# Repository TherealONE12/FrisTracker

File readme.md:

# FrisTracker

A GPS tracking device embedded in an Frisbee disc to capture real-time movement data during games.

## What it does

FrisTracker records GPS coordinates during a frisbee game and wirelessly transmits them to a laptop in real-time. The data can show throwing patterns, strategies, and field coverage throughout a match.

## Why it exists

At my Youth club, we are obsesssed with Ultimate Frisbee. However, as we have lost last years anual Cup to another youth club, we were all devestad. So, I Build FrisTracker! It can help us to Analyze our Training games, and spot weaknesses in our Defense (Or more importantly, weaknesses in our Enemys defenses wich we can then exploit to get an very fair advantage)

Also, tracking a flying disc at 60 mph is just fun.

## Hardware

The tracker fits inside a Frisbee disc and includes:
- **ESP32-PICO-V3-02** microcontroller for GPS processing and wireless transmission
- **NEO-6M GPS module** with external antenna for position tracking
- **NRF24L01+PA+LNA** 2.4GHz radio module for real-time data transmission

A separate receiver module plugs into your laptop and captures the incoming GPS data.

The PCB design files are in `hardware/kicad/`. Gerber files for manufacturing are in `hardware/gerbers/fristracker-gerbers.zip`.

## Bill of Materials

| Part | Purpose | Qty | Unit Price | Total | Vendor |
|------|---------|-----|------------|-------|--------|
| [ESP32-PICO-V3-02](https://de.aliexpress.com/item/1005011934924363.html) | Microcontroller (comes as 2-pack) | 1 | $15.11 | $15.11 | AliExpress |
| [CH340E](https://de.aliexpress.com/item/1005012848940494.html) | USB-to-serial converter | 2 | $6.18 | $12.36 | AliExpress |
| [TLV75733PDRV](https://www.ti.com/product/TLV757P) | 3.3V voltage regulator | 2 | $0.44 | $0.88 | Texas Instruments |
| [NRF24L01+PA+LNA](https://de.aliexpress.com/item/1005008770982853.html) | 2.4GHz wireless transceiver | 2 | $3.84 | $7.68 | AliExpress |
| [NEO-6M GPS](https://de.aliexpress.com/item/1005013019346751.html) | GPS module | 1 | $3.42 | $3.42 | AliExpress |
| [Coin cell holder](https://www.sparkfun.com/coin-cell-battery-holder-12mm-smd.html) | Battery holder for GPS backup | 1 | $0.80 | $0.80 | SparkFun |
| [SMA edge connector](https://www.digikey.com/en/products/detail/rf-solutions/CON-SMA-EDGE-S/5845767) | GPS antenna connector | 1 | $2.75 | $2.75 | DigiKey |
| [GPS antenna](https://de.aliexpress.com/item/1005008618780803.html) | External GPS antenna | 1 | $3.45 | $3.45 | AliExpress |
| | | | **Subtotal** | **$46.45** | |
| | | | **Tax & shipping** | **$15.00** | |
| | | | **Total** | **$61.45** | |

Tax and shipping May vary at your place! - Not included Bill of PCB Files.

## Firmware

The tracker and receiver each run separate Arduino sketches:
- `firmware/tracker.ino` — runs on the disc, reads GPS and transmits data
- `firmware/receiver.ino` — runs on the laptop side, receives and logs data

## Status

Hardware design is complete. Firmware is functional but basic. Building instructions coming soon.

## Project structure

```
FrisTracker/
├── hardware/
│   ├── gerbers/           # Manufacturing files
│   ├── kicad/            # PCB design files
│   └── BOM_base.csv      # Component list
├── firmware/
│   ├── tracker.ino       # Disc-side firmware
│   └── receiver.ino      # Laptop-side firmware
└── docs/
    └── JOURNAL.md        # Development log
```

## License

Open source hardware project. Built as part of Half Life.

Built by Jakob. With lots of <3 and some Bugs :)

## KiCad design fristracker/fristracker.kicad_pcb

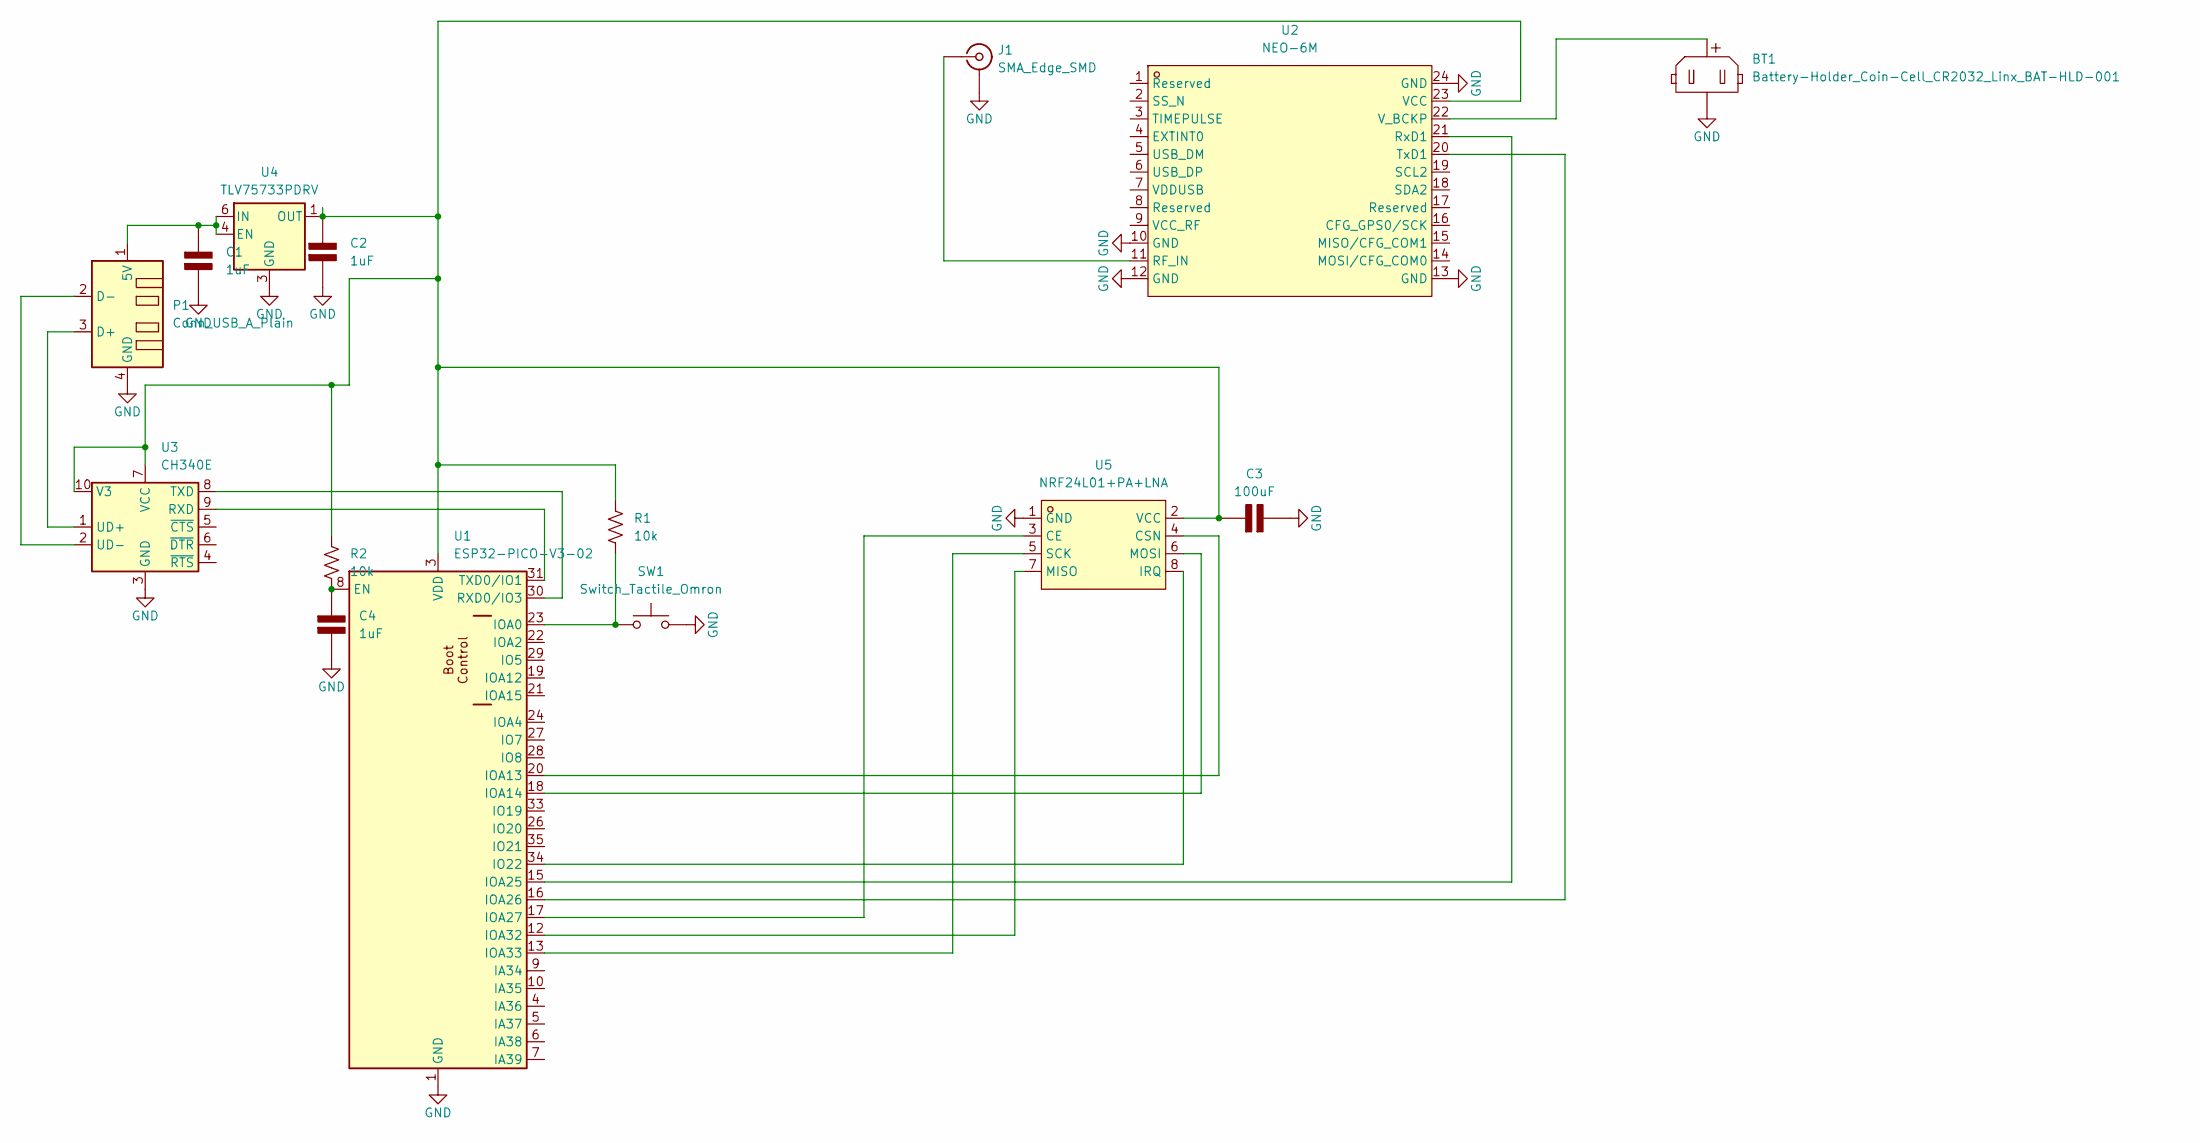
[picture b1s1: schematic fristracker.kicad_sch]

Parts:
BT1: Battery-Holder_Coin-Cell_CR2032_Linx_BAT-HLD-001
C1: 1uF; C_Disc_D5.0mm_W2.5mm_P5.00mm; Rating V
C2, C4: 1uF; C_Disc_D4.3mm_W1.9mm_P5.00mm; Rating V
C3: 100uF; CP_Radial_Tantal_D5.0mm_P5.00mm; Rating V
J1: SMA_Edge_SMD
P1: Conn_USB_A_Plain
R1, R2: 10k; R_0603_1608Metric
SW1: Switch_Tactile_Omron; Button_Omron_B3SN_6.0x6.0mm
U1: ESP32-PICO-V3-02; ESP32-PICO-MINI
U2: NEO-6M; GPSM-SMD_24P-L16.0-W12.2-P1.10; MPN NEO-6M; LCSC Part C2927633
U3: CH340E; MSOP-10_3x3mm_P0.5mm
U4: TLV75733PDRV; WDFN-6_2x2mm
U5: NRF24L01+PA+LNA; COMM-TH_L41.0-W15.5-P2.54_NRF24L01; MPN nRF24L01+PA+LNA; LCSC Part C9900187674

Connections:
GND: BT1.2 (-), C1.2 (-), C2.2 (-), C3.2 (-), C4.2 (-), J1.2 (Ext), P1.4 (GND), SW1.2, U1.1 (GND), U1.2 (GND), U1.11 (GND), U1.14 (GND), U1.36 (GND), U1.37 (GND), U1.38 (GND), U1.39 (GND), U1.40 (GND), U1.41 (GND), U1.42 (GND), U1.43 (GND), U1.44 (GND), U1.45 (GND), U1.46 (GND), U1.47 (GND), U1.48 (GND), U1.49.1 (GND), U1.49.2 (GND), U1.49.3 (GND), U1.49.4 (GND), U1.49.5 (GND), U1.49.6 (GND), U1.49.7 (GND), U1.49.8 (GND), U1.49.9 (GND), U1.50 (GND), U1.51 (GND), U1.52 (GND), U1.53 (GND), U2.10 (GND), U2.12 (GND), U2.13 (GND), U2.24 (GND), U3.3 (GND), U4.3 (GND), U4.7 (GND), U5.1 (GND)
unnamed: BT1.1 (+), U2.22 (V_BCKP)
unnamed: C1.1 (+), P1.1 (5V), U4.4 (EN), U4.6 (IN)
unnamed: C2.1 (+), C3.1 (+), R1.1, R2.1, U1.3 (VDD), U2.23 (VCC), U3.7 (VCC), U3.10 (V3), U4.1 (OUT), U5.2 (VCC)
unnamed: C4.1 (+), R2.2, U1.8 (EN)
unnamed: J1.1 (In), U2.11 (RF_IN)
unnamed: P1.3 (D+), U3.1 (UD+)
unnamed: P1.2 (D-), U3.2 (UD-)
unnamed: U1.34 (IO22), U5.8 (IRQ)
unnamed: R1.2, SW1.1, U1.23 (IOA0)
unnamed: U1.20 (IOA13), U5.4 (CSN)
unnamed: U1.18 (IOA14), U5.6 (MOSI)
unnamed: U1.15 (IOA25), U2.21 (RxD1)
unnamed: U1.16 (IOA26), U2.20 (TxD1)
unnamed: U1.17 (IOA27), U5.3 (CE)
unnamed: U1.12 (IOA32), U5.7 (MISO)
unnamed: U1.13 (IOA33), U5.5 (SCK)
unnamed: U1.30 (RXD0/IO3), U3.8 (TXD)
unnamed: U1.31 (TXD0/IO1), U3.9 (RXD)

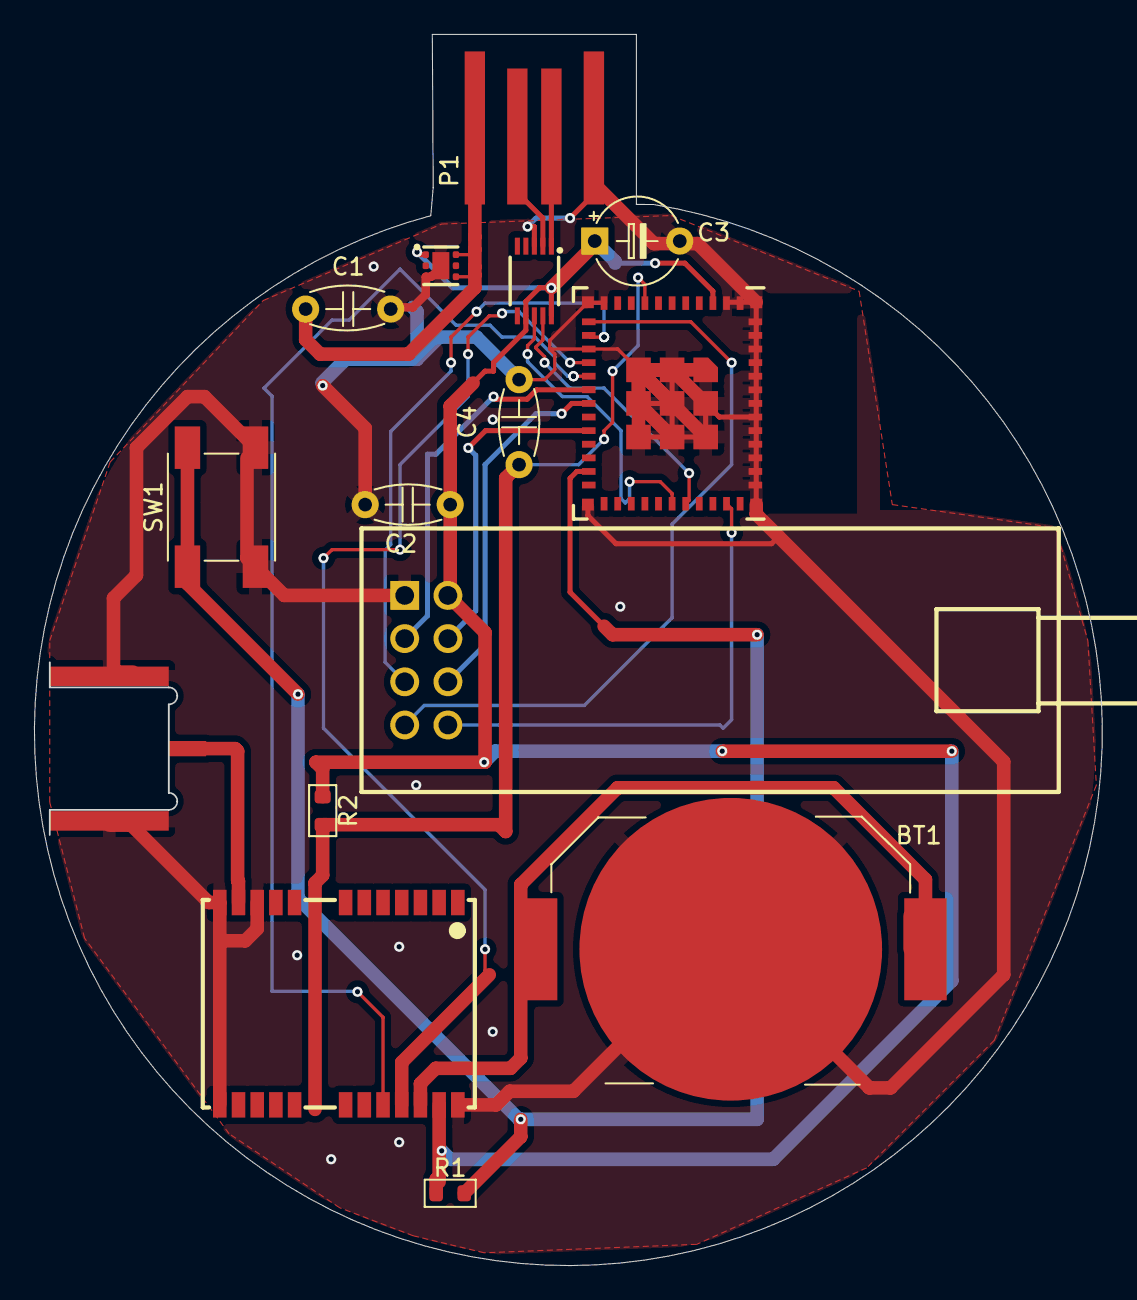
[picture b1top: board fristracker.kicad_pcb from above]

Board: 2 copper layers, 62.8 x 72.4 mm, 15 parts (0 on the bottom side), 19 nets.
